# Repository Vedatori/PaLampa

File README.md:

# PaLampa [cz]
PaLampa je chytrá stolní lampička navržená jako výrobek na Letní robotický tábor 2023 organizovaný spolkem [Vědátoři](www.vedatori.cz). 
Jedná se o výrobek speciálně vyvinutý tak, aby si na něm člověk mohl zlepšit dovednosti při mechanické stavbě, pájení a programování. 
Účastníci dostali tento výrobek jako stavebnici, kdy pájeli nestandardní součástky na DPS s předem osazenými SMD součástkami a z předem připravených dílů sestavili mechanickou část. 
Po finalizaci je možné výrobek programovat a díky množství vstupních a výstupních periferií si naprogramované funkcionality přehledně demonstrovat. 
Nakonec je výrobek možné použít jako chytrou a praktickou stolní lampičku. 

Mechanickou část lze rozdělit na dvě hlavní části - spodní krabici a horní lampu. Vnější části krabice jsou vyřezány z překližky na laserové řezačce a obsahují zámkové západky. 
Ty se při stavbě lepí disperzním lepidlem a po vyschnutí tvoří pevný základ pro uložení ostatních dílů. 
Základní díl horní lampy je vytisknutý na 3D tiskárně a světelný difuzor je vyřezán z plexiskla, které bylo následně zmatněno. 
Spojení osmiček a krabice zajišťuje 3D tištěný nosník umístěný uvnitř krabice, který také fixuje desky plošných spojů (DPS). 
Spojení krabice a lampy zajišťuje překližkový nosník napojený skrze ohebné kouby, kdy spodní kloub disponuje aretací v několika polohách. 

Hlavní DPS obsahuje zejména mikrokontroler ESP32, který je na ni připájen. Programování a napájení je zajištěno přes USB-C. 
Hlavní DPS obsahuje také tlačítka, dotyková tlačítka, potenciometr, fotorezistory, teplotní senzor, OLED grafickou obrazovku a bzučák. 
V lampě je vsazena DPS osazená LED světly svítícími teplou a studenou bílou, stejně jako řadou adresovatelných RGB LED. Další takové LED jsou umístěny zezadu na nosníku, kde zajišťují ambientní podsvětlení prostoru za výrobkem. 
Výrobek je rozebiratelný, jednotlivé DPS jsou spojeny konektory, vzdálenější periferie pomocí kabelů.

Všechny periferie byly zvoleny tak, aby vytvořily výrobek s mnoha volitelnými postranními funkcionalitami. 
Díky nim je možné u účastníků tábora rozvíjet jejich schopnost algoritmizovat úlohu a programovat. 
Pro hodiny byla vytvořena softwarová knihovna, která výrazně zjednodušuje interakci s periferiemi. 
Pomocí této knihovny byl vytvořen vzorový software, pomocí kterého je možné výrobek používat v základním nastavení. 
Výrobek je možné ovládat pomocí vstupních periferií nebo přes WiFi skrz počítač nebo smartphone, které přistupojí k interně hostované webové stránce. 
Všechny tyto vlastnosti lze upravovat a přidávat nové funkcionality podle přání uživatele. Zařízení se programuje ve Visual studio Code v jazyce C++ pomocí frameworku esp32-arduino.

Myšlenkou tohoto projektu je, aby výrobek tvořil každodenní užitečný doplněk pokoje, ale aby mohl být jeho software jednoduše modifikován a rozvíjen tak, jak si každý jeho vlastník představuje.

## Návod
Při stavbě hodin Time-O-Mat postupujte podle připravených návodů v následujícím pořadí:
1. [Návod pro elektroniku](https://github.com/Vedatori/PaLampa/blob/main/Manuals/PaLampa_electronics_cz.md)
1. [Návod pro mechaniku](https://github.com/Vedatori/PaLampa/blob/main/Manuals/PaLampa_mechanics_cz.md)
1. [Návod pro programování](https://github.com/Vedatori/PaLampa/blob/main/Manuals/PaLampa_programming_cz.md)
1. [Lekce na programování](https://github.com/Vedatori/PaLampa/blob/main/Manuals/PaLampa_lectures_achievements.md)

# PaLampa [en]
PaLampa is a smart desk lamp designed as a product for the Summer Robotics Camp 2023 organized by the association Vědátoři. It is a product specially developed to help individuals improve their skills in mechanical construction, soldering, and programming. Participants received this product as a kit, where they soldered non-standard components onto a PCB with pre-mounted SMD components and assembled the mechanical part from pre-prepared pieces. After completion, the product can be programmed, and the programmed functionalities can be easily demonstrated thanks to the variety of input and output peripherals. In the end, the product can be used as a smart and practical desk lamp.

The mechanical part can be divided into two main components - the bottom box and the upper lamp. The outer parts of the box are laser-cut from plywood and include locking mechanisms. These are glued together with dispersion adhesive during construction, forming a sturdy foundation for the placement of other components.
The core component of the upper lamp is 3D-printed, and the light diffuser is cut from frosted plexiglass. The connection between the box and the lamp is ensured by a 3D-printed beam located inside the box, which also secures the printed circuit boards (PCBs).
The connection between the box and the lamp is facilitated by a plywood beam connected through flexible joints, with the lower joint having several locking positions.

The main PCB (Printed Circuit Board) primarily features the ESP32 microcontroller, which is soldered onto it. Programming and power supply are provided through USB-C. The main PCB also includes buttons, touch buttons, a potentiometer, photoresistors, a temperature sensor, an OLED graphic display, and a buzzer.
In the lamp, there is a PCB embedded with warm and cool white LEDs, as well as a series of addressable RGB LEDs. Additional LEDs of this kind are positioned at the rear on the beam, providing ambient lighting for the area behind the product. The product is modular, and the individual PCBs are connected via connectors, while remote peripherals are linked using cables.

All peripherals were selected to create a product with many optional side functionalities. Thanks to these features, participants in the camp can develop their ability to algorithmize tasks and program. A software library was developed for the lessons, significantly simplifying the interaction with peripherals. Using this library, a sample software was created that allows the product to be used in its basic configuration.
The product can be controlled through input peripherals or via Wi-Fi using a computer or smartphone connecting to an internally hosted web page. All of these features can be customized, and new functionalities can be added as per the user's desires. The device is programmed in Visual Studio Code using the C++ language and the esp32-arduino framework.

The idea behind this project is for the product to serve as an everyday useful addition to a room, but with software that can be easily modified and expanded as envisioned by each owner.

## Licence
* Obsah tohoto repozitáře mimo složku *Software* je sdílen pod licencí [Attribution-NonCommercial-ShareAlike 4.0 International (CC BY-NC-SA 4.0)](https://creativecommons.org/licenses/by-nc-sa/4.0/).
* Obsah složky *Software* je sdílen pod licencí [GNU Lesser General Public License v3.0](https://www.gnu.org/licenses/lgpl-3.0.en.html).

## License
* The contents of this repository excluding folder *Software* is shared under license [Attribution-NonCommercial-ShareAlike 4.0 International (CC BY-NC-SA 4.0)](https://creativecommons.org/licenses/by-nc-sa/4.0/).
* The contents of the folder *Software* is shared under license [GNU Lesser General Public License v3.0](https://www.gnu.org/licenses/lgpl-3.0.en.html).

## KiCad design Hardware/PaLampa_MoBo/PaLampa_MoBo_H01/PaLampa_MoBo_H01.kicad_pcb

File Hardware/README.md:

# HW Designer's notes
## I2C addresses
+ OLED Display - `0x3C`
+ FUSB302 - `0x22`

## Current consumptions
+ Board's idle current consumption (with overhead) - ESP and OLED running, no LEDs - 150 - 200 mA
+ WW or CW string at 100% duty (without board's idle consumption) - 1400mA, the current consumption is approximately linear with the PWM duty cycle

## Misc
+ Potentiometer is wired backwards (eg. ADC value decreases when turning counter clockwise) - change it in the next Rev or in SW
+ Current sense resistor in the CC LED driver was probably DoA, check who's fault it was, maybye use 1206 reistors for current spikes from charged capacitors when connecting LEDs to running driver
+ Some LEDs were not soldered correctly - there is probably nothing I can do about it, just beware.
+ Change WW pin to IO17 (Pin 28), internal pullup on IO5 caused short flash on startup / ESP reset. The situation is much better on GPIO17, but for some reason the WW strings still flash on startup (but not on ESP rst, which is weird, might look into it later with more boards assembled).
+ Add JST for Neopixel
+ New Vedatori Logo

## 17.05.2023 - Developer's meeting
+ Add temperature measurement to LED board
+ Add milled grooves to LED board edges for better cooling
+ Add JST 3 pin for neopixel LEDs onto mainboard and create new Neopixel channel
+ Move one photoresistor to the back, switch it with the electrolytic capacitor, move the second photoresistor somewhere near
+ Add "do not remove while running" text near connectors 
+ Add 2 pin JST for touch
+ move buzzer

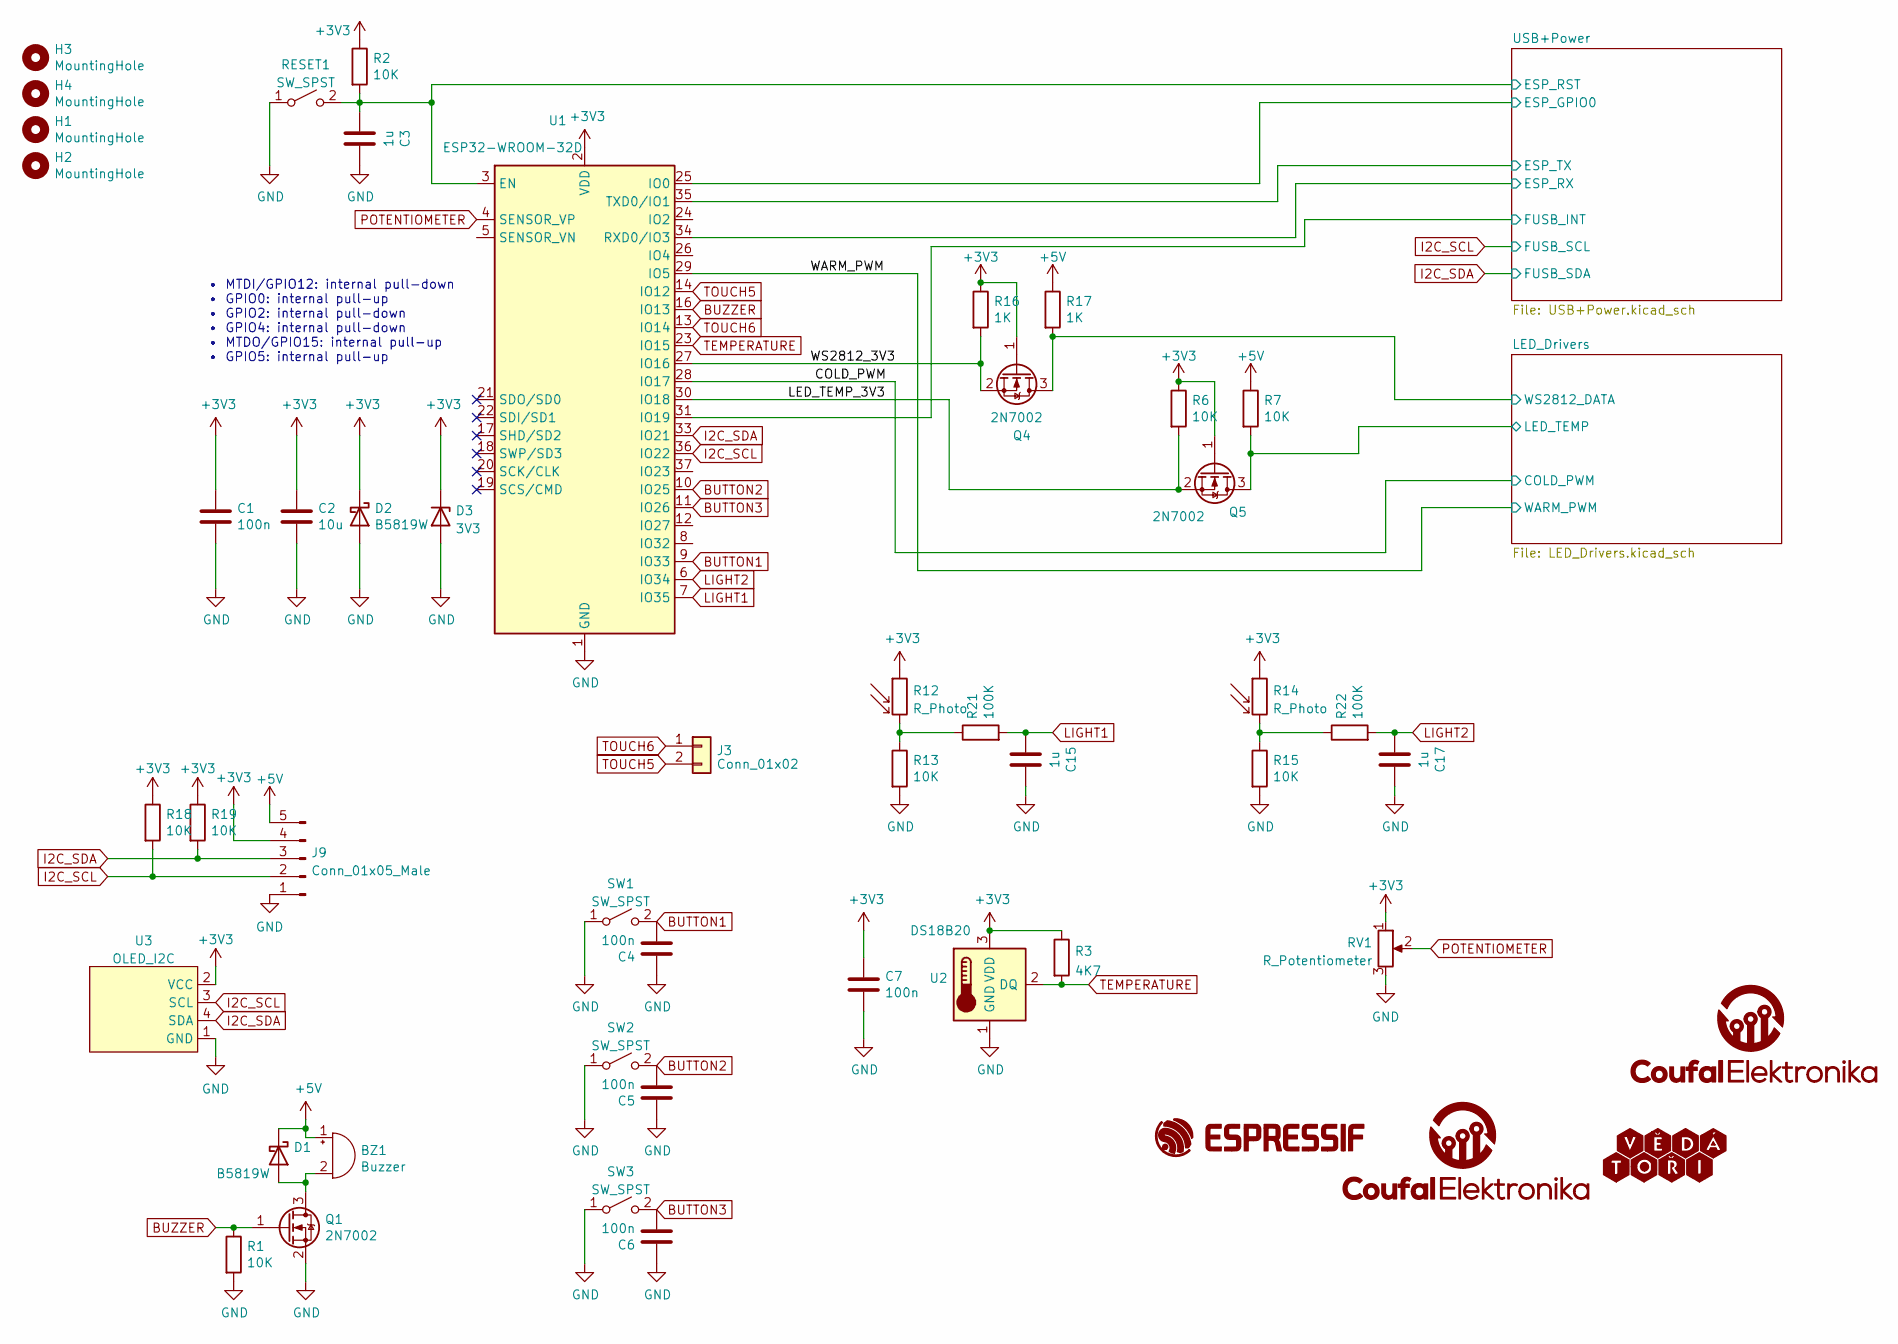
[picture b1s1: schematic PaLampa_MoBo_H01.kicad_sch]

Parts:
BZ1: Buzzer; Buzzer_12x9.5RM6.6
C1, C4, C5, C6, C7: 100n; C_0603_1608Metric; LCSC C14663
C2: 10u; C_0805_2012Metric; LCSC C15850
C3, C15, C17: 1u; C_0603_1608Metric; LCSC C15849
D1, D2: B5819W; D_SOD-123; LCSC C8598
D3: 3V3; D_MiniMELF; LCSC C8056
G1: CoufalElektronika_logo; Coufal_elektronika_text_30x13mm
G2: Vedatori_logo; VedatoriNew_40x5,7mm
G4: CoufalElektronika_logo; Coufal_elektronika_notext_10mm
G5: Espressif_logo; Espressif_logo_30mm
H1, H2, H3, H4: MountingHole; MountingHole_3.2mm_M3
J3: Conn_01x02; JST_XH_B2B-XH-A_1x02_P2.50mm_Vertical
J9: Conn_01x05_Male; PinHeader_1x05_P2.54mm_Vertical
Q1, Q4, Q5: 2N7002; SOT-23; LCSC C8545
R1, R2, R6, R7, R13, R15, R18, R19: 10K; R_0603_1608Metric; LCSC C25804
R3: 4K7; R_0603_1608Metric; LCSC C23162
R12, R14: R_Photo; R_LDR_5.1x4.3mm_P3.4mm_Vertical
R16, R17: 1K; R_0603_1608Metric; LCSC C21190
R21, R22: 100K; R_0603_1608Metric; LCSC C25803
RESET1: SW_SPST; SW_SPST_TL3342; LCSC C318884
RV1: R_Potentiometer; Potentiometer_Alps_RK09K_Single_Vertical
SW1, SW2, SW3: SW_SPST; SW_PUSH_6mm_H13mm
U1: ESP32-WROOM-32D; ESP32-WROOM-32; LCSC C529577
U2: DS18B20; TO-92_HandSolder
U3: OLED_I2C; Display_128x64_096_I2C_3Hole

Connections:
+3V3: C1.1, C2.1, C7.1, D2.1 (K), D3.1 (K), J9.4, Q4.1 (G), Q5.1 (G), R2.1, R3.1, R6.1, R12.1, R14.1, R16.1, R18.1, R19.1, RV1.1, U1.2 (VDD), U2.3 (VDD), U3.2 (VCC); also elsewhere on the board
+5V: BZ1.1 (-), D1.1 (K), J9.5, R7.1, R17.1; also elsewhere on the board
/COLD_PWM: U1.28 (IO17); also elsewhere on the board
/LED_Drivers/LED_TEMP: Q5.3 (D), R7.2; also elsewhere on the board
/LED_Drivers/WS2812_DATA: Q4.3 (D), R17.2; also elsewhere on the board
/LED_TEMP_3V3: Q5.2 (S), R6.2, U1.30 (IO18)
/USB+Power/ESP_GPIO0: U1.25 (IO0); also elsewhere on the board
/USB+Power/ESP_RST: C3.2, R2.2, RESET1.2 (B), U1.3 (EN); also elsewhere on the board
/USB+Power/ESP_RX: U1.34 (RXD0/IO3); also elsewhere on the board
/USB+Power/ESP_TX: U1.35 (TXD0/IO1); also elsewhere on the board
/USB+Power/FUSB_INT: U1.31 (IO19); also elsewhere on the board
/WARM_PWM: U1.29 (IO5); also elsewhere on the board
/WS2812_3V3: Q4.2 (S), R16.2, U1.27 (IO16)
BUTTON1: C4.2, SW1.2 (B), U1.9 (IO33)
BUTTON2: C5.2, SW2.2 (B), U1.10 (IO25)
BUTTON3: C6.2, SW3.2 (B), U1.11 (IO26)
BUZZER: Q1.1 (G), R1.1, U1.16 (IO13)
GND: C1.2, C2.2, C3.1, C4.1, C5.1, C6.1, C7.2, C15.1, C17.1, D2.2 (A), D3.2 (A), J9.1, Q1.2 (S), R1.2, R13.2, R15.2, RESET1.1 (A), RV1.3, SW1.1 (A), SW2.1 (A), SW3.1 (A), U1.1 (GND), U1.15 (GND), U1.38 (GND), U1.39 (GND), U2.1 (GND), U3.1 (GND); also elsewhere on the board
I2C_SCL: J9.2, R18.2, U1.36 (IO22), U3.3 (SCL); also elsewhere on the board
I2C_SDA: J9.3, R19.2, U1.33 (IO21), U3.4 (SDA); also elsewhere on the board
LIGHT1: C15.2, R21.2, U1.7 (IO35)
LIGHT2: C17.2, R22.2, U1.6 (IO34)
unnamed: BZ1.2 (+), D1.2 (A), Q1.3 (D)
unnamed: R12.2, R13.1, R21.1
unnamed: R14.2, R15.1, R22.1
POTENTIOMETER: RV1.2, U1.4 (SENSOR_VP)
TEMPERATURE: R3.2, U1.23 (IO15), U2.2 (DQ)
TOUCH5: J3.2, U1.14 (IO12)
TOUCH6: J3.1, U1.13 (IO14)

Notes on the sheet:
• MTDI/GPIO12: internal pull-down • GPIO0: internal pull-up • GPIO2: internal pull-down • GPIO4: internal pull-down • MTDO/GPIO15: internal pull-up • GPIO5: internal pull-up

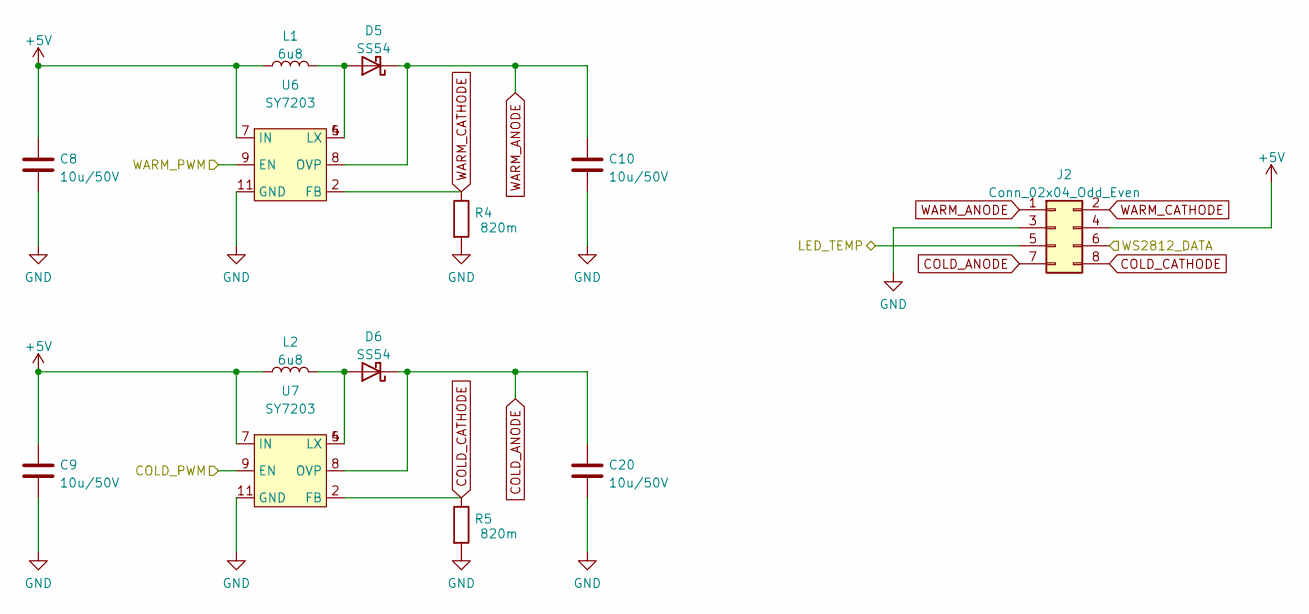
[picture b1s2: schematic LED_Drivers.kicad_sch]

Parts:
C8, C9, C10, C20: 10u/50V; C_1206_3216Metric; LCSC C13585
D5, D6: SS54; D_SMA; LCSC C22452
J2: Conn_02x04_Odd_Even; IDC-Header_2x04_P2.54mm_Vertical
L1, L2: 6u8; L_Cenker_CKCS5040; LCSC C354608
R4, R5: 820m; R_1206_3216Metric; LCSC C175854
U6, U7: SY7203; DFN-10-1EP_3x3mm_P0.5mm_EP1.75x2.6mm; LCSC C125894

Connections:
+5V: C8.1, C9.1, J2.4, L1.1, L2.1, U6.7 (IN), U7.7 (IN); also elsewhere on the board
/COLD_PWM: U7.9 (EN); also elsewhere on the board
/LED_Drivers/LED_TEMP: J2.5; also elsewhere on the board
/LED_Drivers/WS2812_DATA: J2.6; also elsewhere on the board
/WARM_PWM: U6.9 (EN); also elsewhere on the board
COLD_ANODE: C20.1, D6.1 (K), J2.7, U7.8 (OVP)
COLD_CATHODE: J2.8, R5.1, U7.2 (FB)
GND: C8.2, C9.2, C10.2, C20.2, J2.3, R4.2, R5.2, U6.11 (GND), U7.11 (GND); also elsewhere on the board
unnamed: D5.2 (A), L1.2, U6.4 (LX), U6.5 (LX)
unnamed: D6.2 (A), L2.2, U7.4 (LX), U7.5 (LX)
WARM_ANODE: C10.1, D5.1 (K), J2.1, U6.8 (OVP)
WARM_CATHODE: J2.2, R4.1, U6.2 (FB)

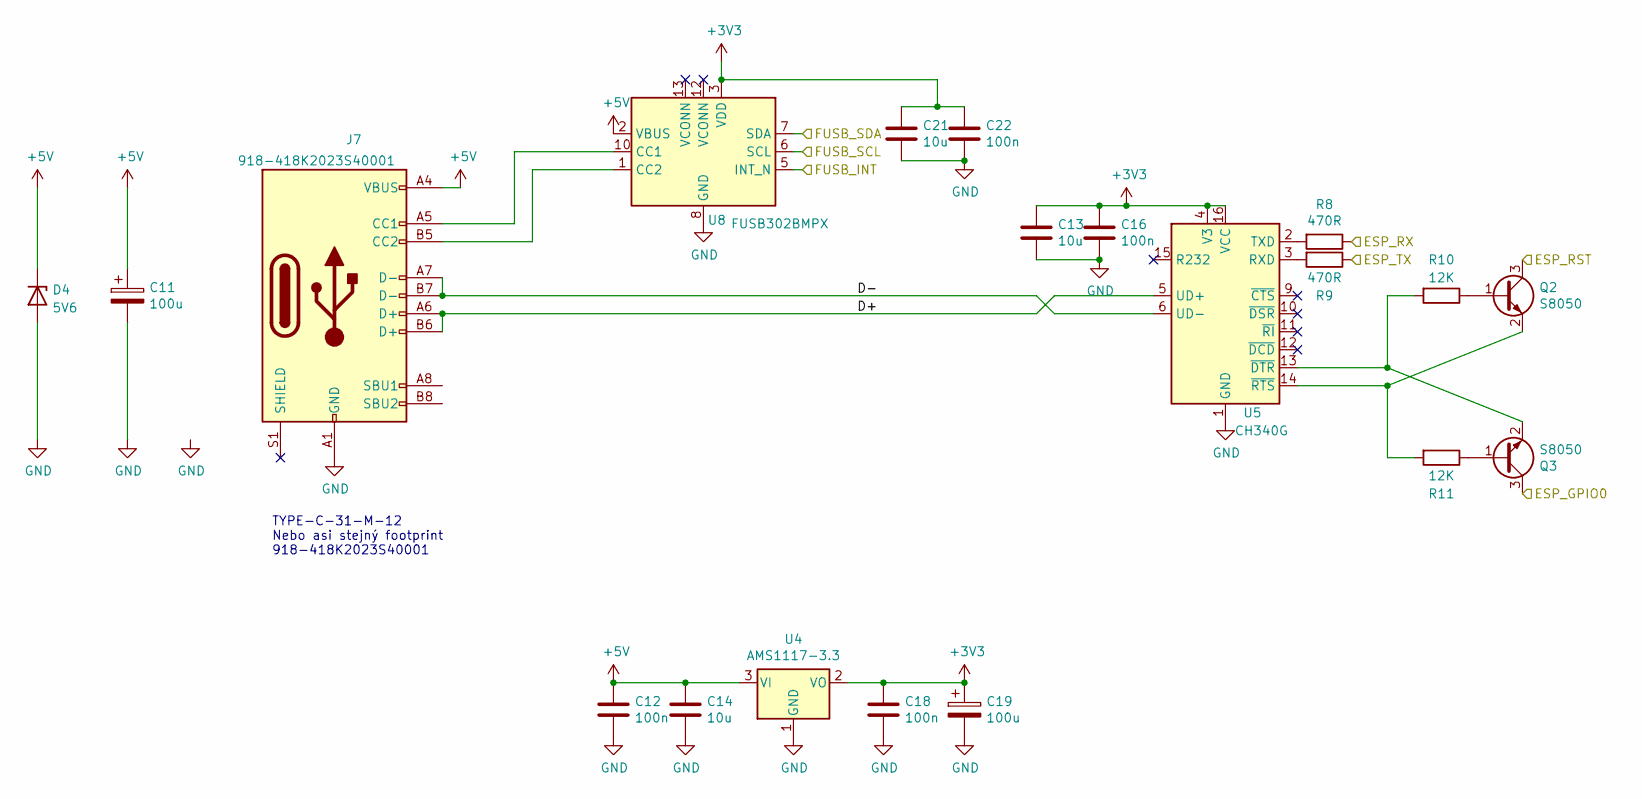
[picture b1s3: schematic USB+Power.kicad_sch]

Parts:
C11, C19: 100u; CP_Radial_D5.0mm_P2.00mm; LCSC C43348
C12, C16, C18, C22: 100n; C_0603_1608Metric; LCSC C14663
C13, C21: 10u; C_0603_1608Metric; LCSC C19702
C14: 10u; C_0805_2012Metric; LCSC C15850
D4: 5V6; D_MiniMELF; LCSC C8062
J7: 918-418K2023S40001; USB_C_Receptacle_HRO_TYPE-C-31-M-12; LCSC C167321
Q2, Q3: S8050; SOT-23; LCSC C2146
R8, R9: 470R; R_0603_1608Metric; LCSC C23179
R10, R11: 12K; R_0603_1608Metric; LCSC C22790
U4: AMS1117-3.3; SOT-223-3_TabPin2; LCSC C6186
U5: CH340G; SOIC-16_3.9x9.9mm_P1.27mm; LCSC C84681
U8: FUSB302BMPX; WQFN-14-1EP_2.5x2.5mm_P0.5mm_EP1.45x1.45mm; LCSC C132291

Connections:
+3V3: C13.1, C16.1, C18.1, C19.1, C21.1, C22.1, U4.2 (VO), U5.4 (V3), U5.16 (VCC), U8.3 (VDD), U8.4 (VDD); also elsewhere on the board
+5V: C11.1, C12.1, C14.1, D4.1 (K), J7.A4 (VBUS), J7.A9 (VBUS), J7.B4 (VBUS), J7.B9 (VBUS), U4.3 (VI), U8.2 (VBUS); also elsewhere on the board
/USB+Power/D+: J7.A6 (D+), J7.B6 (D+), U5.5 (UD+)
/USB+Power/D-: J7.A7 (D-), J7.B7 (D-), U5.6 (UD-)
/USB+Power/ESP_GPIO0: Q3.3 (C); also elsewhere on the board
/USB+Power/ESP_RST: Q2.3 (C); also elsewhere on the board
/USB+Power/ESP_RX: R8.1; also elsewhere on the board
/USB+Power/ESP_TX: R9.1; also elsewhere on the board
/USB+Power/FUSB_INT: U8.5 (INT_N); also elsewhere on the board
GND: C11.2, C12.2, C13.2, C14.2, C16.2, C18.2, C19.2, C21.2, C22.2, D4.2 (A), J7.A1 (GND), J7.A12 (GND), J7.B1 (GND), J7.B12 (GND), U4.1 (GND), U5.1 (GND), U8.8 (GND), U8.9 (GND), U8.15 (GND); also elsewhere on the board
I2C_SCL: U8.6 (SCL); also elsewhere on the board
I2C_SDA: U8.7 (SDA); also elsewhere on the board
unnamed: J7.A5 (CC1), U8.10 (CC1), U8.11 (CC1)
unnamed: J7.B5 (CC2), U8.1 (CC2), U8.14 (CC2)
unnamed: Q2.1 (B), R10.1
unnamed: Q2.2 (E), R11.2, U5.14 (~RTS)
unnamed: Q3.1 (B), R11.1
unnamed: Q3.2 (E), R10.2, U5.13 (~DTR)
unnamed: R9.2, U5.3 (RXD)
unnamed: R8.2, U5.2 (TXD)

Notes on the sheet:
TYPE-C-31-M-12 Nebo asi stejný footprint 918-418K2023S40001

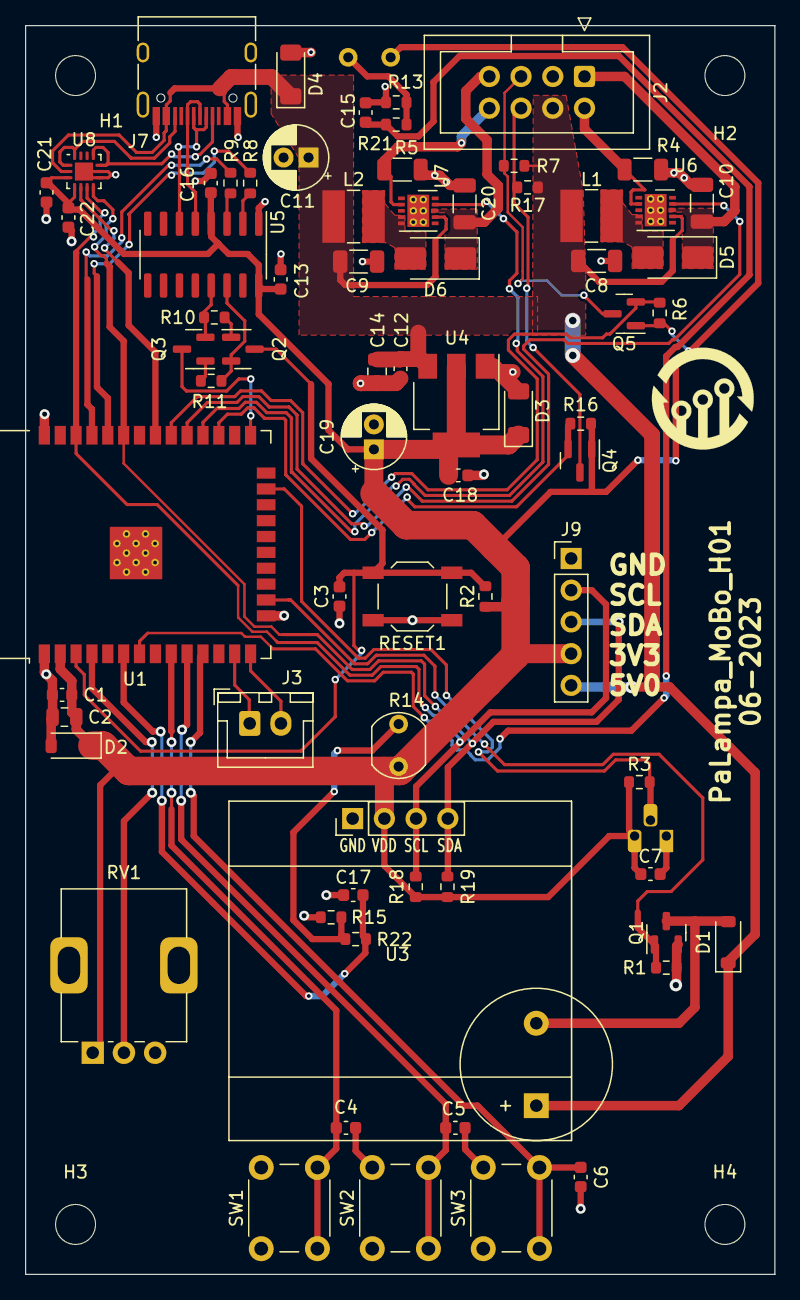
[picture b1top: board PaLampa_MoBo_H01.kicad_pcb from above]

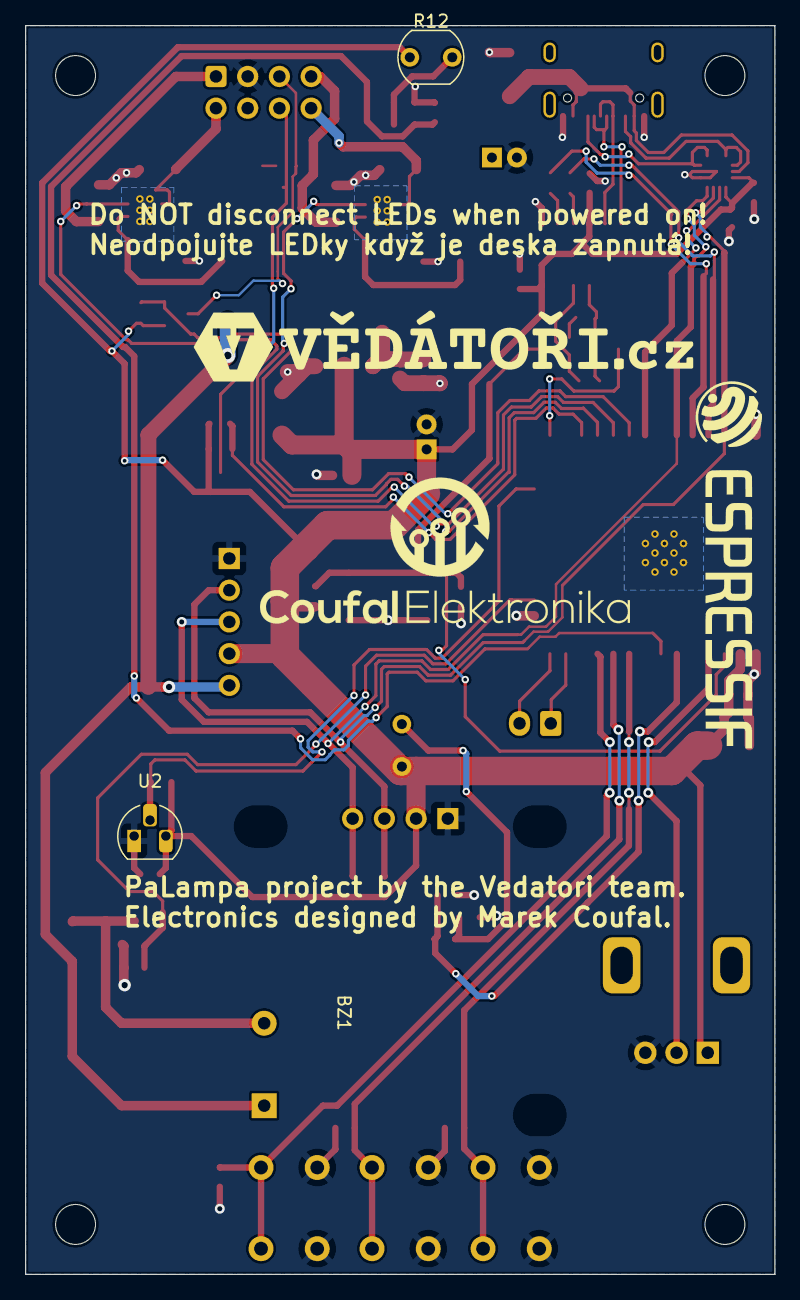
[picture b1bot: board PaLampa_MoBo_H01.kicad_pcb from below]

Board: 2 copper layers, 60.0 x 100.0 mm, 82 parts (5 on the bottom side), 45 nets.

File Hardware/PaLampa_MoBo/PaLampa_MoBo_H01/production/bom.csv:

Designator,Footprint,Quantity,Value,LCSC Part #
BZ1,Buzzer_12x9.5RM6.6,1,Buzzer,
"C1, C12, C16, C18, C22, C4, C5, C6, C7",0603,9,100n,C14663
"C10, C20, C8, C9",1206,4,10u/50V,C13585
"C11, C19",CP_Radial_D5.0mm_P2.00mm,2,100u,C43348
"C13, C21",0603,2,10u,C19702
"C14, C2",0805,2,10u,C15850
"C15, C17, C3",0603,3,1u,C15849
"D1, D2",D_SOD-123,2,B5819W,C8598
D3,D_MiniMELF,1,3V3,C8056
D4,D_MiniMELF,1,5V6,C8062
"D5, D6",D_SMA,2,SS54,C22452
J2,IDC-Header_2x04_P2.54mm_Vertical,1,Conn_02x04_Odd_Even,
J3,JST_XH_B2B-XH-A_1x02_P2.50mm_Vertical,1,Conn_01x02,
J7,USB_C_Receptacle_HRO_TYPE-C-31-M-12,1,918-418K2023S40001,C167321
J9,PinHeader_1x05_P2.54mm_Vertical,1,Conn_01x05_Male,
"L1, L2",L_Cenker_CKCS5040,2,6u8,C354608
"Q1, Q4, Q5",SOT-23,3,2N7002,C8545
"Q2, Q3",SOT-23,2,S8050,C2146
"R1, R13, R15, R18, R19, R2, R6, R7",0603,8,10K,C25804
"R10, R11",0603,2,12K,C22790
"R12, R14",R_LDR_5.1x4.3mm_P3.4mm_Vertical,2,R_Photo,
"R16, R17",0603,2,1K,C21190
"R21, R22",0603,2,100K,C25803
R3,0603,1,4K7,C23162
"R4, R5",1206,2,820m,C175854
"R8, R9",0603,2,470R,C23179
RESET1,SW_SPST_TL3342,1,SW_SPST,C318884
RV1,Potentiometer_Alps_RK09K_Single_Vertical,1,R_Potentiometer,
"SW1, SW2, SW3",SW_PUSH_6mm_H13mm,3,SW_SPST,
U1,ESP32-WROOM-32,1,ESP32-WROOM-32D,C529577
U2,TO-92_HandSolder,1,DS18B20,
U3,Display_128x64_096_I2C_3Hole,1,OLED_I2C,
U4,SOT-223-3_TabPin2,1,AMS1117-3.3,C6186
U5,SOIC-16_3.9x9.9mm_P1.27mm,1,CH340G,C84681
"U6, U7",DFN-10-1EP_3x3mm_P0.5mm_EP1.75x2.6mm,2,SY7203,C125894
U8,WQFN-14-1EP_2.5x2.5mm_P0.5mm_EP1.45x1.45mm,1,FUSB302BMPX,C132291

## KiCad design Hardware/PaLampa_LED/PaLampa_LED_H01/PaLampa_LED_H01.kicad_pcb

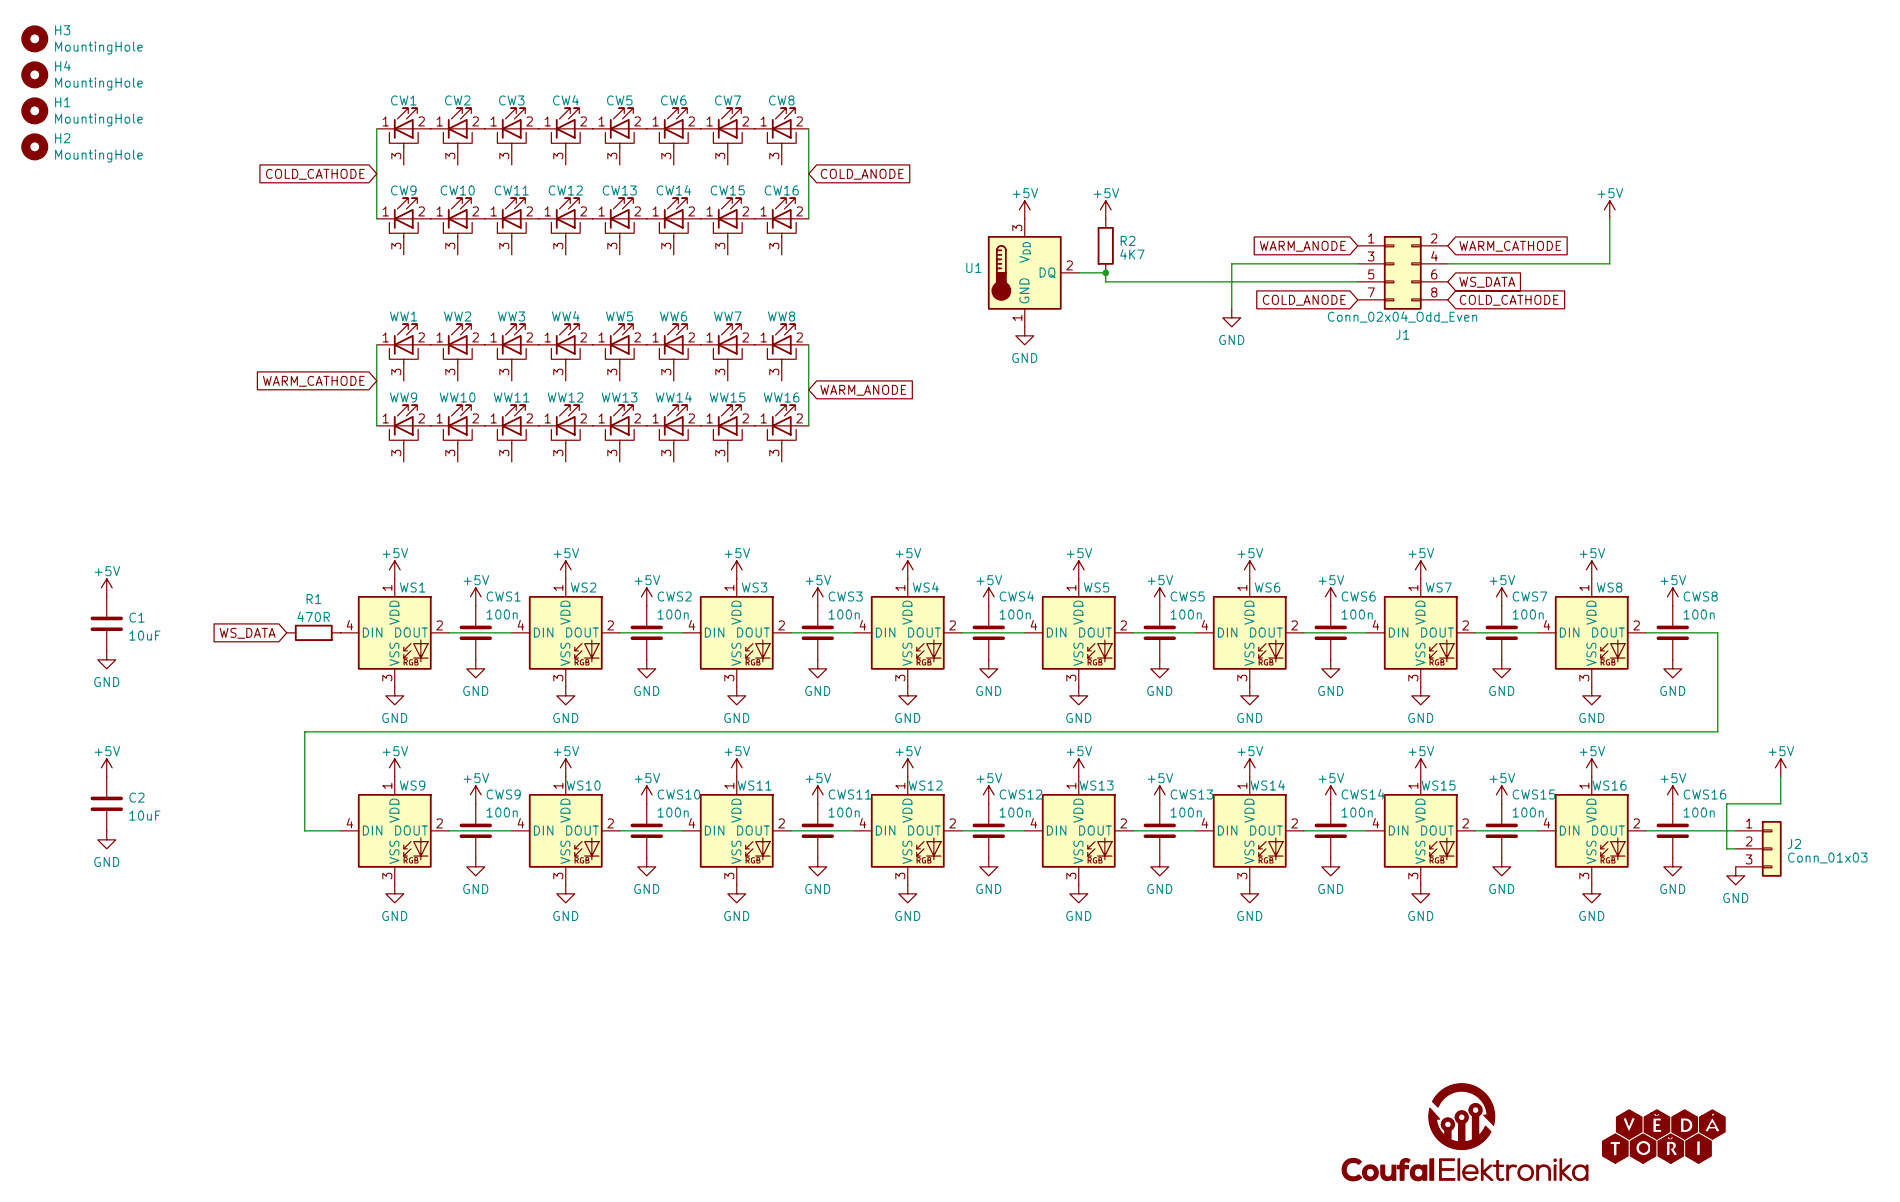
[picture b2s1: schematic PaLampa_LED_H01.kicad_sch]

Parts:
C1, C2: 10uF; C_0603_1608Metric; LCSC C19702
CW1, CW2, CW3, CW4, CW5, CW6, CW7, CW8, CW9, CW10, CW11, CW12, CW13, CW14, CW15, CW16: HL-A-5730D1W-S1-08-HR3(LY); HL-A-5730; LCSC C210348
CWS1, CWS2, CWS3, CWS4, CWS5, CWS6, CWS7, CWS8, CWS9, CWS10, CWS11, CWS12, CWS13, CWS14, CWS15, CWS16: 100n; C_0402_1005Metric; LCSC C1525
G1: CoufalElektronika_logo; Coufal_elektronika_notext_10mm
G2: Vedatori_logo; VedatoriNew_40x5,7mm
H1, H2, H3, H4: MountingHole; MountingHole_3.2mm_M3
J1: Conn_02x04_Odd_Even; IDC-Header_2x04_P2.54mm_Horizontal
J2: Conn_01x03; JST_XH_S3B-XH-A_1x03_P2.50mm_Horizontal
R1: 470R; R_0402_1005Metric; LCSC C25117
R2: 4K7; R_0402_1005Metric; LCSC C25900
U1: DS18B20; TO-92_Inline
WS1, WS2, WS3, WS4, WS5, WS6, WS7, WS8, WS9, WS10, WS11, WS12, WS13, WS14, WS15, WS16: XL-5050RGBC-WS2812B; LED_WS2812B_PLCC4_5.0x5.0mm_P3.2mm; LCSC C2843785
WW1, WW2, WW3, WW4, WW5, WW6, WW7, WW8, WW9, WW10, WW11, WW12, WW13, WW14, WW15, WW16: HL-A-5730D34W-S1-08-HR3(LY); HL-A-5730; LCSC C210345

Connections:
+5V: C1.1, C2.1, CWS1.1, CWS2.1, CWS3.1, CWS4.1, CWS5.1, CWS6.1, CWS7.1, CWS8.1, CWS9.1, CWS10.1, CWS11.1, CWS12.1, CWS13.1, CWS14.1, CWS15.1, CWS16.1, J1.4, J2.2, R2.1, U1.3 (V_{DD}), WS1.1 (VDD), WS2.1 (VDD), WS3.1 (VDD), WS4.1 (VDD), WS5.1 (VDD), WS6.1 (VDD), WS7.1 (VDD), WS8.1 (VDD), WS9.1 (VDD), WS10.1 (VDD), WS11.1 (VDD), WS12.1 (VDD), WS13.1 (VDD), WS14.1 (VDD), WS15.1 (VDD), WS16.1 (VDD)
COLD_ANODE: CW8.2 (A), CW16.2 (A), J1.7
COLD_CATHODE: CW1.1 (K), CW9.1 (K), J1.8
GND: C1.2, C2.2, CWS1.2, CWS2.2, CWS3.2, CWS4.2, CWS5.2, CWS6.2, CWS7.2, CWS8.2, CWS9.2, CWS10.2, CWS11.2, CWS12.2, CWS13.2, CWS14.2, CWS15.2, CWS16.2, J1.3, J2.3, U1.1 (GND), WS1.3 (VSS), WS2.3 (VSS), WS3.3 (VSS), WS4.3 (VSS), WS5.3 (VSS), WS6.3 (VSS), WS7.3 (VSS), WS8.3 (VSS), WS9.3 (VSS), WS10.3 (VSS), WS11.3 (VSS), WS12.3 (VSS), WS13.3 (VSS), WS14.3 (VSS), WS15.3 (VSS), WS16.3 (VSS)
unnamed: CW1.2 (A), CW2.1 (K)
unnamed: CW2.2 (A), CW3.1 (K)
unnamed: CW3.2 (A), CW4.1 (K)
unnamed: CW4.2 (A), CW5.1 (K)
unnamed: CW5.2 (A), CW6.1 (K)
unnamed: CW6.2 (A), CW7.1 (K)
unnamed: CW7.2 (A), CW8.1 (K)
unnamed: CW10.2 (A), CW11.1 (K)
unnamed: CW9.2 (A), CW10.1 (K)
unnamed: CW11.2 (A), CW12.1 (K)
unnamed: CW12.2 (A), CW13.1 (K)
unnamed: CW13.2 (A), CW14.1 (K)
unnamed: CW14.2 (A), CW15.1 (K)
unnamed: CW15.2 (A), CW16.1 (K)
unnamed: J1.5, R2.2, U1.2 (DQ)
unnamed: J2.1, WS16.2 (DOUT)
unnamed: R1.2, WS1.4 (DIN)
unnamed: WS1.2 (DOUT), WS2.4 (DIN)
unnamed: WS2.2 (DOUT), WS3.4 (DIN)
unnamed: WS3.2 (DOUT), WS4.4 (DIN)
unnamed: WS4.2 (DOUT), WS5.4 (DIN)
unnamed: WS5.2 (DOUT), WS6.4 (DIN)
unnamed: WS6.2 (DOUT), WS7.4 (DIN)
unnamed: WS7.2 (DOUT), WS8.4 (DIN)
unnamed: WS8.2 (DOUT), WS9.4 (DIN)
unnamed: WS9.2 (DOUT), WS10.4 (DIN)
unnamed: WS10.2 (DOUT), WS11.4 (DIN)
unnamed: WS11.2 (DOUT), WS12.4 (DIN)
unnamed: WS12.2 (DOUT), WS13.4 (DIN)
unnamed: WS13.2 (DOUT), WS14.4 (DIN)
unnamed: WS14.2 (DOUT), WS15.4 (DIN)
unnamed: WS15.2 (DOUT), WS16.4 (DIN)
unnamed: WW1.2 (A), WW2.1 (K)
unnamed: WW2.2 (A), WW3.1 (K)
unnamed: WW3.2 (A), WW4.1 (K)
unnamed: WW4.2 (A), WW5.1 (K)
unnamed: WW5.2 (A), WW6.1 (K)
unnamed: WW6.2 (A), WW7.1 (K)
unnamed: WW7.2 (A), WW8.1 (K)
unnamed: WW10.2 (A), WW11.1 (K)
unnamed: WW9.2 (A), WW10.1 (K)
unnamed: WW11.2 (A), WW12.1 (K)
unnamed: WW12.2 (A), WW13.1 (K)
unnamed: WW13.2 (A), WW14.1 (K)
unnamed: WW14.2 (A), WW15.1 (K)
unnamed: WW15.2 (A), WW16.1 (K)
WARM_ANODE: J1.1, WW8.2 (A), WW16.2 (A)
WARM_CATHODE: J1.2, WW1.1 (K), WW9.1 (K)
WS_DATA: J1.6, R1.1

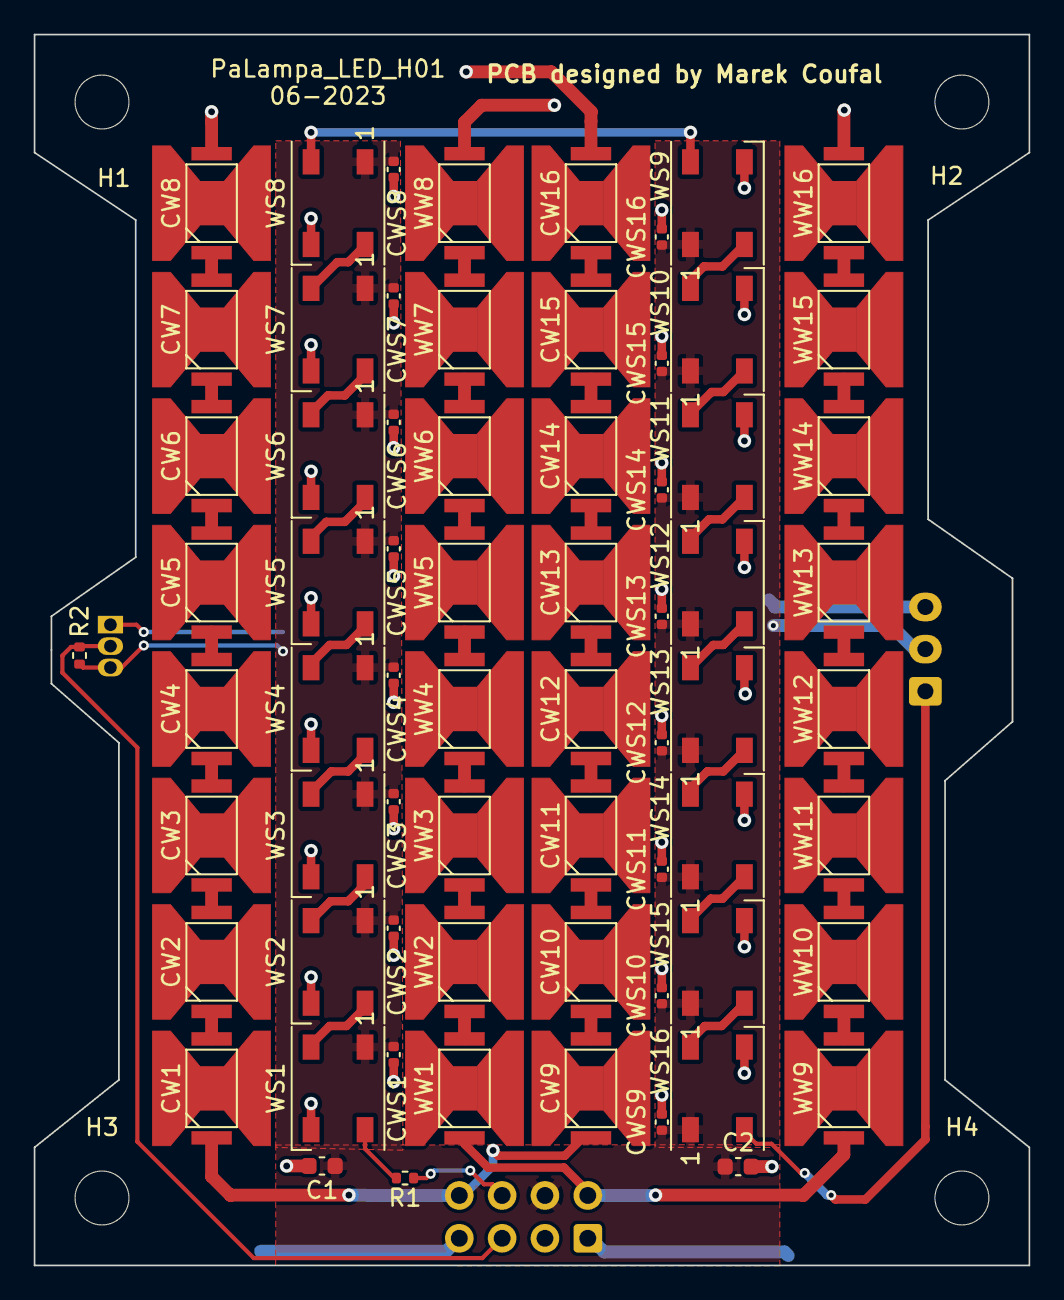
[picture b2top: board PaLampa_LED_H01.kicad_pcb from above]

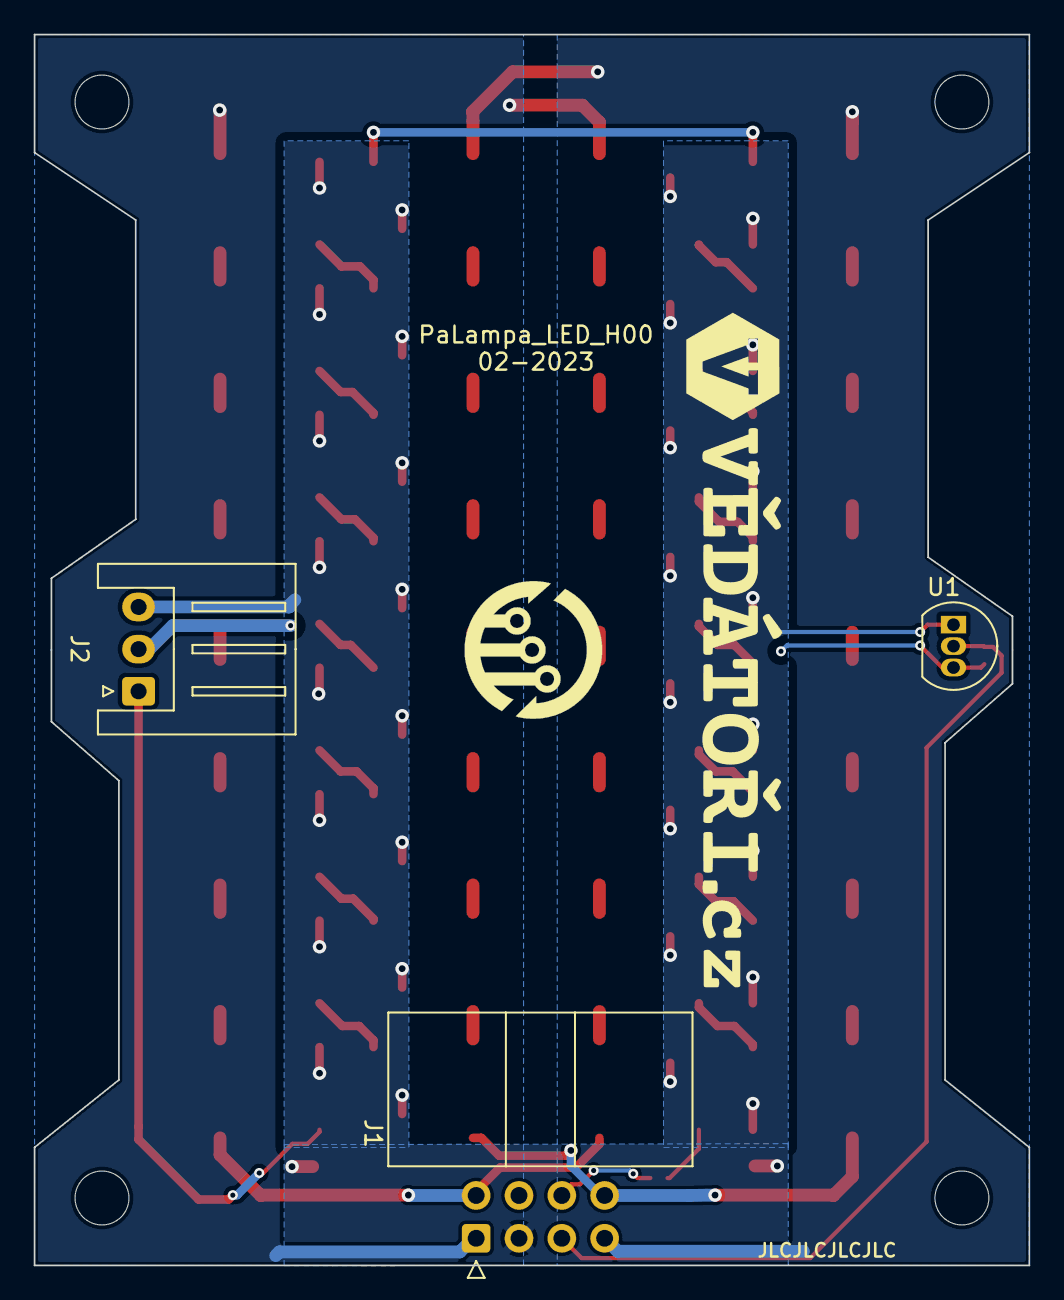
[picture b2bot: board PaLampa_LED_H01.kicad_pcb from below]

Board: 2 copper layers, 59.0 x 73.0 mm, 77 parts (5 on the bottom side), 53 nets.

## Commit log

2023-01-18 Added License
2023-01-30 First HW commit
2023-02-09 HW updates
2023-03-19 MoBo changes, exported LED step
2023-03-19 Updated projects to KiCad 7.0
2023-04-13 Completed H00 revision. Added production data.
2023-04-14 changed electrolytic capacitor part number
2023-05-01 Added HW notes
2023-05-02 readme update
2023-05-02 HW readme update
2023-06-11 Update HW Readme.
2023-06-12 Cloned boards for H01 revisions.
2023-06-15 H01 changes
2023-06-15 LED board H01 update
2023-06-15 H01 update
2023-06-15 H01 updates
2023-06-16 H01 release
2023-07-26 First demo Palampa lib.
2023-08-01 New Photoresistor module.
2023-08-06 New Thermometer module.
2023-08-09 Time module initial commit
2023-08-10 Implemented additional time.h functions
2023-08-11 Added Time_module features
2023-08-12 Mechanical manual pt.1
2023-08-12 Electronics manual v1
2023-08-12 El manual bug fix
2023-08-13 El manual bug fix again (crappy images)
2023-08-13 Electronics manual fix
2023-08-13 Fixed capacitive Cu strip info.
2023-08-13 Added missing manual picture
2023-08-13 Lights module draft.
2023-08-13 Mechanical manual update
2023-08-13 Lights module working implementation.
2023-08-13 Light module power limit.
2023-08-13 Mechanic manual update 2
2023-08-13 Mechanic manual v3
2023-08-13 Programming manual update.
2023-08-14 Mechanical manual fix.
2023-08-14 Mechanical manual LED stripe orientation fix.
2023-08-15 Using RGB 0-1 ranges.
2023-08-15 test
2023-08-15 lekce 1-2
    změny názvů ukolu a ....
2023-08-15 time o mat to palampa
2023-08-15 ()
    přidání závorek
2023-08-15 lekce 3
    piezo
2023-08-15 uprava ukol 1
2023-08-15 lekce4-5
2023-08-15 update ukol
2023-08-15 lekce6
2023-08-15 lekce 1
2023-08-15 cisla
2023-08-15 L1+L2 update
2023-08-15 lekce 6-7
2023-08-15 lekce 1 úkol 1
2023-08-15 lekce8
2023-08-15 lekce 2
2023-08-15 lekce 9
2023-08-15 presun lekce 4
2023-08-15 RGB to HSV
2023-08-15 Lekce 4
2023-08-15 Fixed LED exponential transition and LED refreshing.
2023-08-15 lekce komplet
2023-08-15 oddelani ()
2023-08-15 Oled display init commit
2023-08-15 Improved time module
2023-08-15 little fix
2023-08-15 Lekce 6
2023-08-16 Transitions for white LEDs.
2023-08-16 Lekce 8
2023-08-16 Lekce (#1)
    * test
    * lekce 1-2
    změny názvů ukolu a ....
    * time o mat to palampa
    * ()
    přidání závorek
2023-08-16 Fixed ledc channels and button modes setup.
2023-08-16 Lectures update
2023-08-17 Fix all example codes
2023-08-17 Capacitive button library added
2023-08-17 uprava ukolu 11
2023-08-17 moved lections and added serial to temp lection
2023-08-17 fixed little bugs in code
2023-08-17 Time-module bugfix
2023-08-17 fixed lections (#4)
    * Fix all example codes
    * moved lections and added serial to temp lection
    * fixed little bugs in code
2023-08-17 Time module (#5)
    * Time module initial commit
    * Implemented additional time.h functions
    * Added Time_module features
    * Improved time module
    * Time-module bugfix
2023-08-17 Added were not gonna take it melody
2023-08-17 Capacitive button library added to programming manual
2023-08-17 Updated time module usage.
2023-08-17 Prog manual fix.
2023-08-17 Limiting light current to control temperature.
2023-08-17 Temp regulation fix.
2023-08-18 added code highlighting
2023-08-18 last push 1
2023-08-18 Oled module features
2023-08-18 Fixed cap button lections
2023-08-18 Added highlighting to programming guide
2023-08-18 Minimal display manual.
2023-08-18 White lights temperature functions
2023-08-18 Fix touch sensor update.
2023-08-18 feat: Add OTA update for FS and SPIFFS
2023-08-18 Updated display logo.
2023-08-18 Power module basics.
2023-08-18 Update white light temp functions.
2023-08-19 Demo program.
2023-08-22 Czech readme text draft. Updated CapacitiveButton module.
2023-10-20 Add en readme section.
2023-11-09 Mechnics manual fixes and screws list.
2023-12-14 Mechanic manual update. Display time. Webapp name update.
2024-05-21 Add brightness-preserving mode to ()
